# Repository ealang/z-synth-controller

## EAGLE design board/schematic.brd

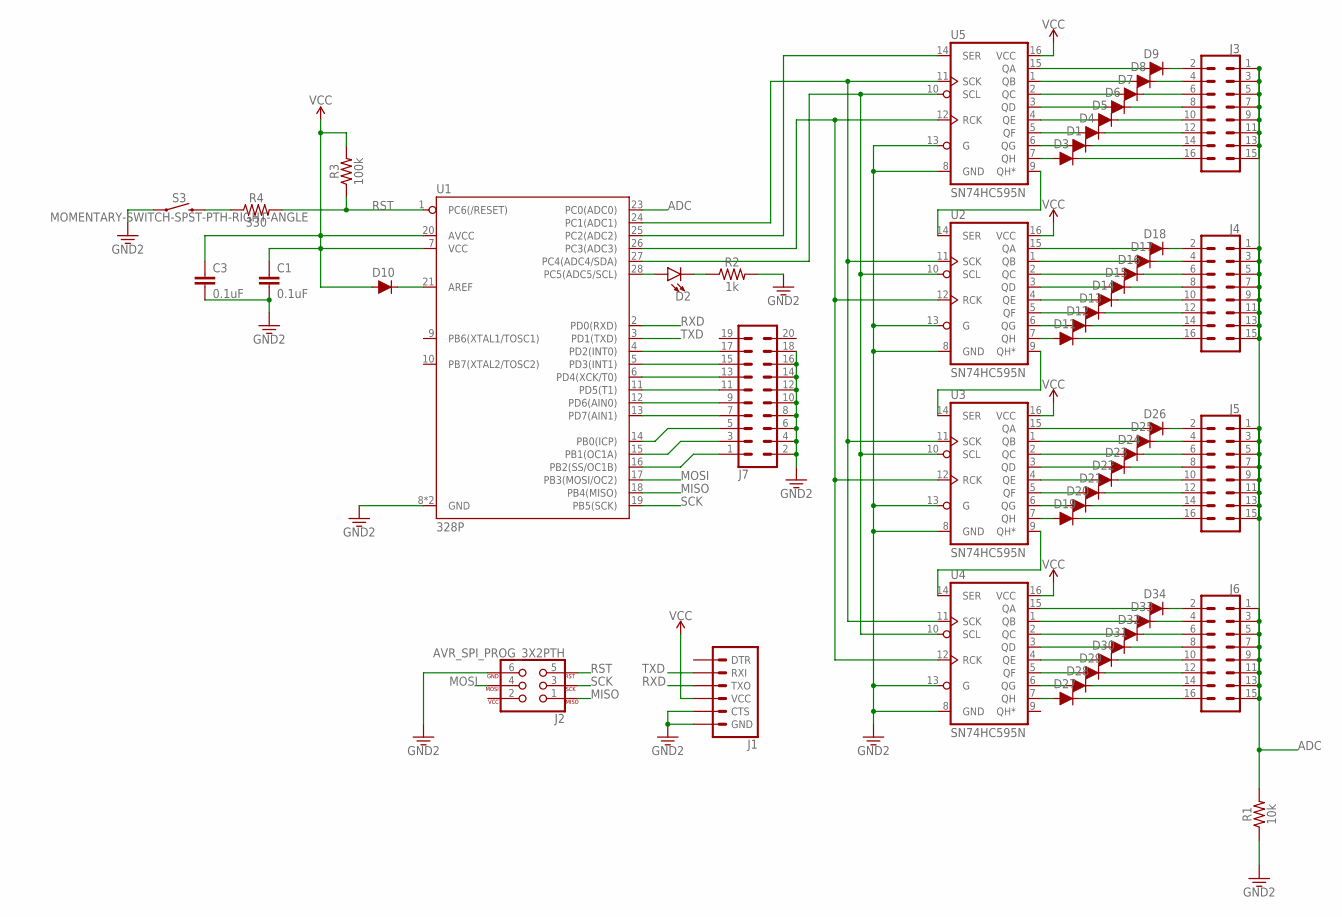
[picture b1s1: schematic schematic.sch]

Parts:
C1, C3: 0.1uF; CAP-PTH-SMALL-KIT
D1, D3, D4, D5, D6, D7, D8, D9, D10, D11, D12, D13, D14, D15, D16, D17, D18, D19, D20, D21, D22, D23, D24, D25, D26, D27, D28, D29, D30, D31, D32, D33, D34: 200mA/100V/1V; DIODE-1N4148
D2: LED5MM; LED_5MM
J1: 6_PIN_SERIAL_TARGETLOCK; 1X06_LOCK
J2: AVR_SPI_PROG_3X2PTH; 2X3
J3, J4, J5, J6: CONN_08X2_HEADER; 2X8
J7: CONN_10X2; 2X10
R1: 10k; AXIAL-0.3
R2: 1k; AXIAL-0.3
R3: 100k; AXIAL-0.3
R4: 330; AXIAL-0.3
S3: MOMENTARY-SWITCH-SPST-PTH-RIGHT-ANGLE; TACTILE_SWITCH_PTH_RIGHT_ANGLE
U1: 328P; DIP28
U2, U3, U4, U5: SN74HC595N; DIP16

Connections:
ADC: J3.1, J3.3, J3.5, J3.7, J3.9, J3.11, J3.13, J3.15, J4.1, J4.3, J4.5, J4.7, J4.9, J4.11, J4.13, J4.15, J5.1, J5.3, J5.5, J5.7, J5.9, J5.11, J5.13, J5.15, J6.1, J6.3, J6.5, J6.7, J6.9, J6.11, J6.13, J6.15, R1.P$2 (2), U1.23 (PC0(ADC0))
GND: C1.2, C3.2, J1.5 (CTS), J1.6 (GND), J2.6, J7.2, J7.4, J7.6, J7.8, J7.10, J7.12, J7.14, J7.16, J7.18, R1.P$1 (1), R2.P$2 (2), S3.1, U1.8 (GND), U1.22 (GND), U2.8 (GND), U2.13 (G), U3.8 (GND), U3.13 (G), U4.8 (GND), U4.13 (G), U5.8 (GND), U5.13 (G)
MISO: J2.1, U1.18 (PB4(MISO))
MOSI: J2.4, U1.17 (PB3(MOSI/OC2))
unnamed: U1.24 (PC1(ADC1)), U2.11 (SCK), U3.11 (SCK), U4.11 (SCK), U5.11 (SCK)
unnamed: D18.A, U2.15 (QA)
unnamed: U1.25 (PC2(ADC2)), U5.14 (SER)
unnamed: U1.26 (PC3(ADC3)), U2.12 (RCK), U3.12 (RCK), U4.12 (RCK), U5.12 (RCK)
unnamed: U1.27 (PC4(ADC4/SDA)), U2.10 (SCL), U3.10 (SCL), U4.10 (SCL), U5.10 (SCL)
unnamed: D9.C, J3.2
unnamed: D8.A, U5.1 (QB)
unnamed: D8.C, J3.4
unnamed: D9.A, U5.15 (QA)
unnamed: D7.A, U5.2 (QC)
unnamed: D7.C, J3.6
unnamed: D6.A, U5.3 (QD)
unnamed: D6.C, J3.8
unnamed: D5.A, U5.4 (QE)
unnamed: D5.C, J3.10
unnamed: D4.A, U5.5 (QF)
unnamed: D4.C, J3.12
unnamed: D1.A, U5.6 (QG)
unnamed: D1.C, J3.14
unnamed: D3.A, U5.7 (QH)
unnamed: D3.C, J3.16
unnamed: U2.14 (SER), U5.9 (QH*)
unnamed: U2.9 (QH*), U3.14 (SER)
unnamed: U3.9 (QH*), U4.14 (SER)
unnamed: D18.C, J4.2
unnamed: D17.C, J4.4
unnamed: D16.C, J4.6
unnamed: D15.C, J4.8
unnamed: D14.C, J4.10
unnamed: D13.C, J4.12
unnamed: D12.C, J4.14
unnamed: D11.C, J4.16
unnamed: D11.A, U2.7 (QH)
unnamed: D12.A, U2.6 (QG)
unnamed: D13.A, U2.5 (QF)
unnamed: D14.A, U2.4 (QE)
unnamed: D15.A, U2.3 (QD)
unnamed: D16.A, U2.2 (QC)
unnamed: D17.A, U2.1 (QB)
unnamed: D26.A, U3.15 (QA)
unnamed: D19.C, J5.16
unnamed: D20.C, J5.14
unnamed: D25.A, U3.1 (QB)
unnamed: D24.A, U3.2 (QC)
unnamed: D21.C, J5.12
unnamed: D22.C, J5.10
unnamed: D23.A, U3.3 (QD)
unnamed: D22.A, U3.4 (QE)
unnamed: D23.C, J5.8
unnamed: D24.C, J5.6
unnamed: D21.A, U3.5 (QF)
unnamed: D20.A, U3.6 (QG)
unnamed: D25.C, J5.4
unnamed: D26.C, J5.2
unnamed: D19.A, U3.7 (QH)
unnamed: D34.A, U4.15 (QA)
unnamed: D27.C, J6.16
unnamed: D28.C, J6.14
unnamed: D29.C, J6.12
unnamed: D30.C, J6.10
unnamed: D31.C, J6.8
unnamed: D32.C, J6.6
unnamed: D33.C, J6.4
unnamed: D34.C, J6.2
unnamed: D27.A, U4.7 (QH)
unnamed: D28.A, U4.6 (QG)
unnamed: D29.A, U4.5 (QF)
unnamed: D30.A, U4.4 (QE)
unnamed: D31.A, U4.3 (QD)
unnamed: D32.A, U4.2 (QC)
unnamed: D33.A, U4.1 (QB)
unnamed: D10.C, U1.21 (AREF)
unnamed: D2.A, U1.28 (PC5(ADC5/SCL))
unnamed: D2.K (C), R2.P$1 (1)
unnamed: J7.1, U1.16 (PB2(SS/OC1B))
unnamed: J7.3, U1.15 (PB1(OC1A))
unnamed: J7.5, U1.14 (PB0(ICP))
unnamed: J7.7, U1.13 (PD7(AIN1))
unnamed: J7.9, U1.12 (PD6(AIN0))
unnamed: J7.11, U1.11 (PD5(T1))
unnamed: J7.13, U1.6 (PD4(XCK/T0))
unnamed: J7.15, U1.5 (PD3(INT1))
unnamed: J7.17, U1.4 (PD2(INT0))
unnamed: R4.P$1 (1), S3.2
RST: J2.5, R3.P$1 (1), R4.P$2 (2), U1.1 (PC6(/RESET))
RXD: J1.3 (TXO), U1.2 (PD0(RXD))
SCK: J2.3, U1.19 (PB5(SCK))
TXD: J1.2 (RXI), U1.3 (PD1(TXD))
VCC: C1.1, C3.1, D10.A, J1.4 (VCC), R3.P$2 (2), U1.7 (VCC), U1.20 (AVCC), U2.16 (VCC), U3.16 (VCC), U4.16 (VCC), U5.16 (VCC)

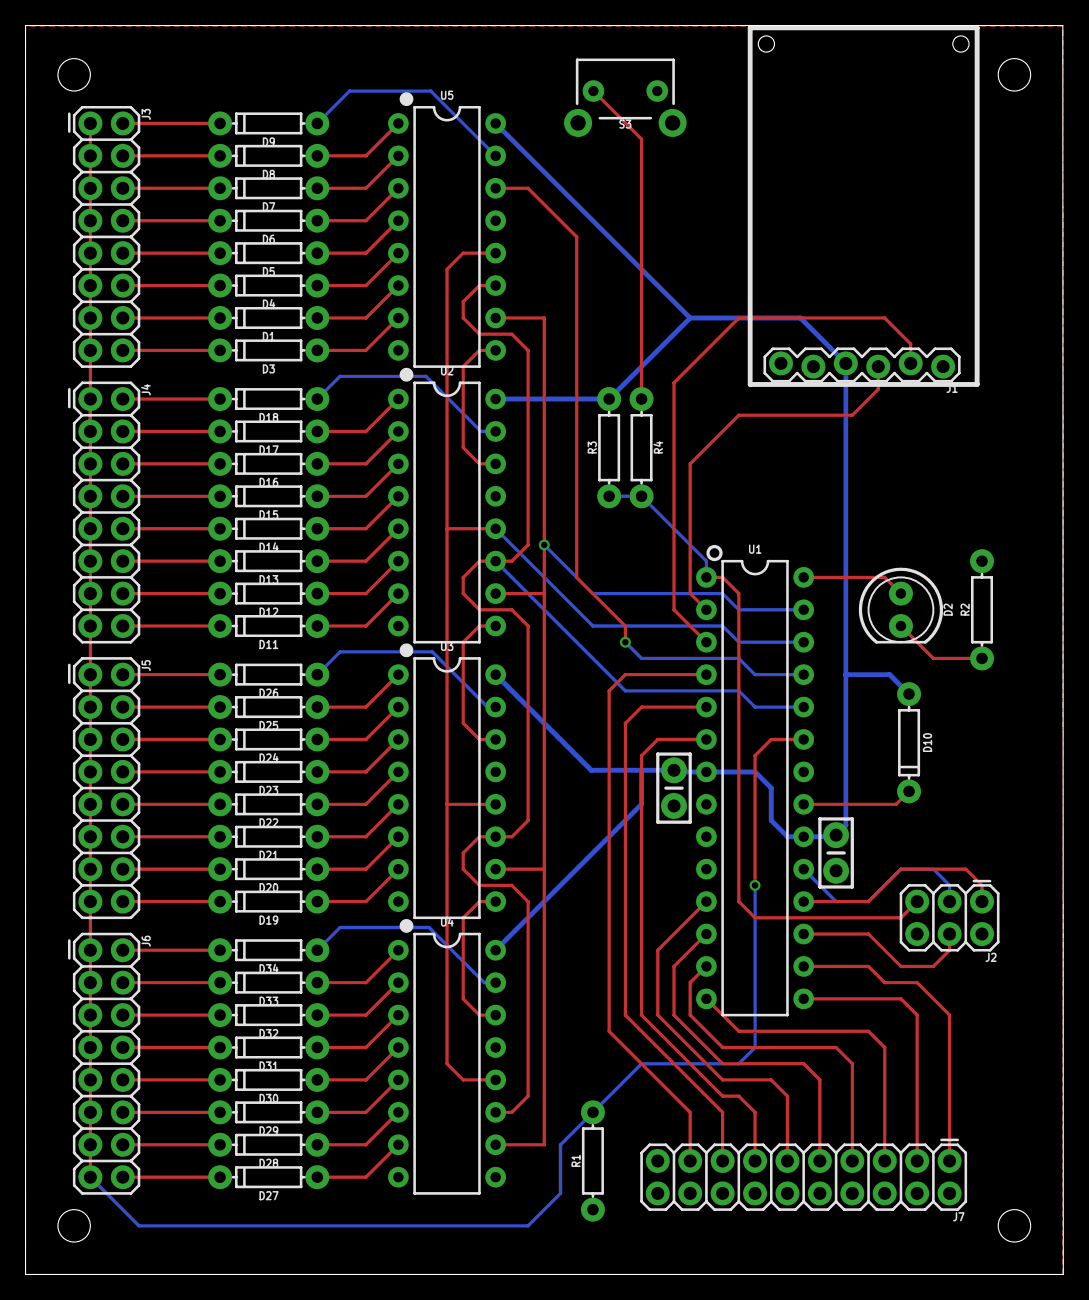
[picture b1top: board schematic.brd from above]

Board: 2 copper layers, 81.3 x 97.8 mm, 53 parts (0 on the bottom side), 93 nets.

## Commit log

2021-03-06 skeleton
2021-03-06 Add select pin
2021-03-06 hacky shift register impl
2021-03-06 Lib to control shift reg
2021-03-06 Implement ADC with select pin via shift reg
2021-03-06 Add change flag
2021-03-07 add spi interface to read values
2021-03-07 Enable optimization
2021-03-14 Wip faceplate
2021-03-14 Reorganize
2021-03-14 Switch driver to usart
2021-03-14 Implement min-max update interval
2021-03-14 Relocate shifter, make atomic
2021-03-14 Add dimmable led
2021-03-15 Add input handling
2021-03-16 cleanup config, makefile
2021-03-16 Refactor adc change poll api
2021-03-17 Implement preset logic
2021-03-19 Rename button input update function for consistency
2021-03-19 Add led sequences
2021-03-21 Basic noise filtering
2021-03-21 Starting point driver
2021-03-21 Detect bounces
2021-03-21 Add rolling average to reduce noise
2021-03-22 Avoid ramp up at start
2021-03-22 Add fuse settings
2021-03-22 Avoid sending redundant nrpn messages
2021-03-22 Add weighted mapping type
2021-03-27 Add eagle project
2021-03-28 Switch to 8 bit adc mode
2021-03-28 Increase to 32 sensors
2021-03-28 Add baudrate param
2021-03-28 Account for pot tolerances, map to linear range
2021-03-28 Cleanup schematic
2021-04-06 Mapping options for n position switch
2021-04-10 Fix crossed rx/tx
2021-04-12 Add calibration config util
2021-10-27 Separate ADC calibration config for easier update
2021-11-15 Add complete config
2023-02-06 Update config
2023-02-07 Wire lfo param select
2023-02-08 Adjust config for easier cutoff

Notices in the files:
parts and their libraries:
SparkFun-Capacitors: Licensing: Creative Commons ShareAlike 4.0 International - https://creativecommons.org/licenses/by-sa/4.0
